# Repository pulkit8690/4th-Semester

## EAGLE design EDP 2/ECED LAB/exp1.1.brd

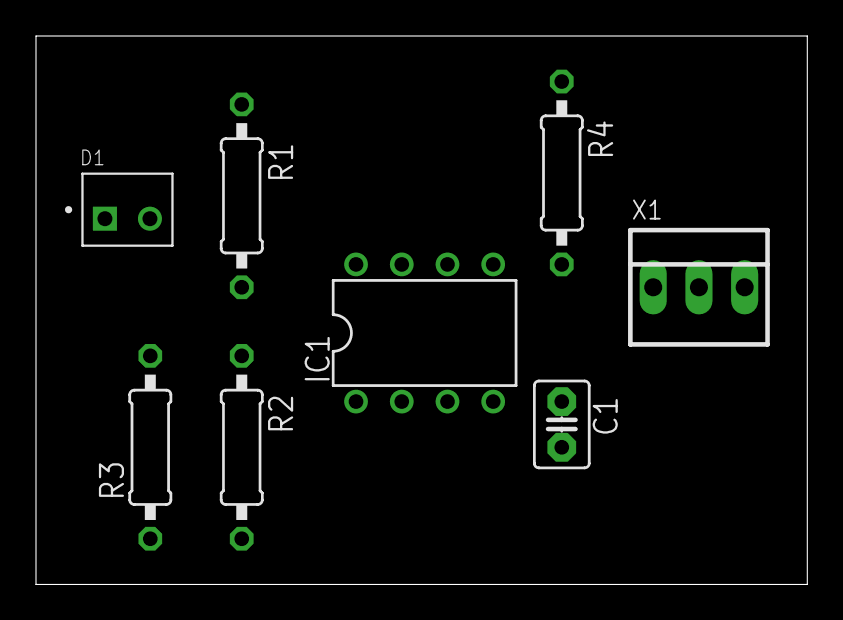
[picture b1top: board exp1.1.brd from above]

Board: 2 copper layers, 42.8 x 30.5 mm, 8 parts (0 on the bottom side), 6 nets, no tracks yet.

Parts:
C1: C2.5-3
D1: BPW41N; DIO_BPW41N
IC1: LM311N; DIL08
R1, R2, R3, R4: 0207/10
X1: 22-23-2031

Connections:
+5V: D1.C, IC1.8, R1.2, R4.2, X1.1
GND: C1.2, IC1.1, IC1.4, R2.1, R3.1, X1.3
unnamed: IC1.3, R1.1, R2.2
unnamed: D1.A, IC1.2, R3.2
unnamed: C1.1, R4.1
unnamed: IC1.7, X1.2

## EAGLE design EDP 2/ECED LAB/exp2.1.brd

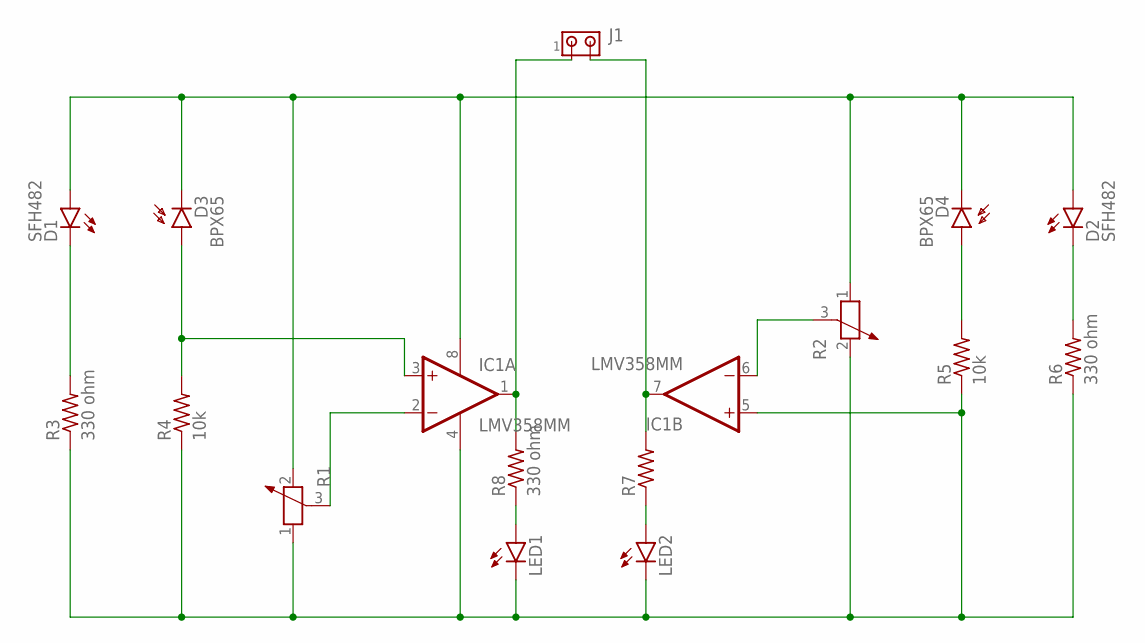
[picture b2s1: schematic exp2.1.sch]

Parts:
D1, D2: SFH482
D3, D4: BPX65
IC1: LMV358MM; MSOP08
J1: MTA02-100; 10X02MTA
LED1, LED2: LED3MM
R1, R2: POTENTIOMETER_PT-10; PT-10
R3, R6, R8: 330 ohm; 0207/10
R4, R5: 10k; 0207/10
R7: R-US_0207/10; 0207/10

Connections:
unnamed: D1.A, D2.A, D3.K (C), D4.K (C), IC1.8 (V+), R1.2, R2.1
unnamed: D1.K (C), R3.2
unnamed: D3.A, IC1.3 (+IN), R4.2
unnamed: IC1.4 (V-), IC1.5 (+IN), LED1.K (C), LED2.K (C), R1.1, R2.2, R3.1, R4.1, R5.1, R6.1
unnamed: D2.K (C), R6.2
unnamed: D4.A, R5.2
unnamed: IC1.1 (OUT), J1.1, R8.2
unnamed: IC1.7 (OUT), J1.2, R7.2
unnamed: IC1.2 (-IN), R1.3
unnamed: IC1.6 (-IN), R2.3
unnamed: LED1.A, R8.1
unnamed: LED2.A, R7.1

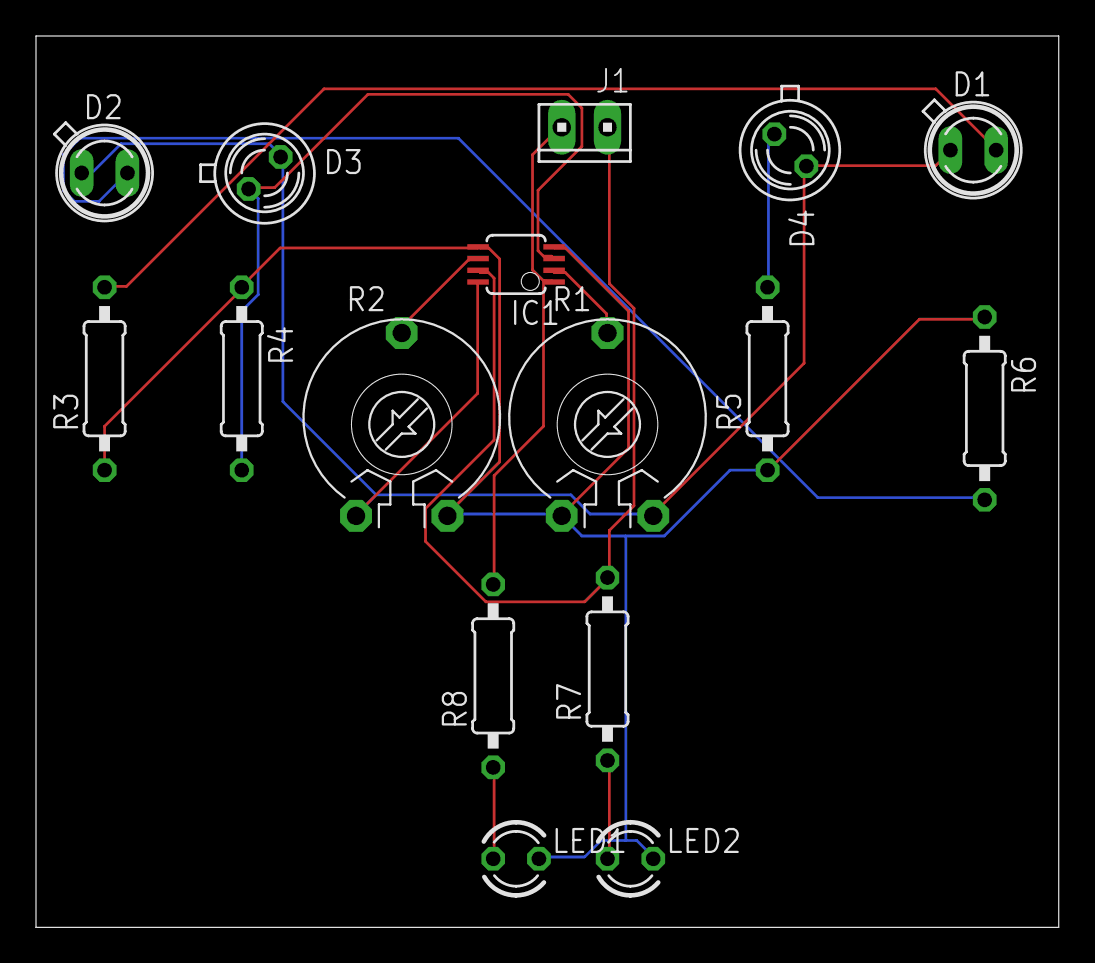
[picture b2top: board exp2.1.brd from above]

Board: 2 copper layers, 56.8 x 49.5 mm, 16 parts (0 on the bottom side), 12 nets.

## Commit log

2024-04-14 complete
